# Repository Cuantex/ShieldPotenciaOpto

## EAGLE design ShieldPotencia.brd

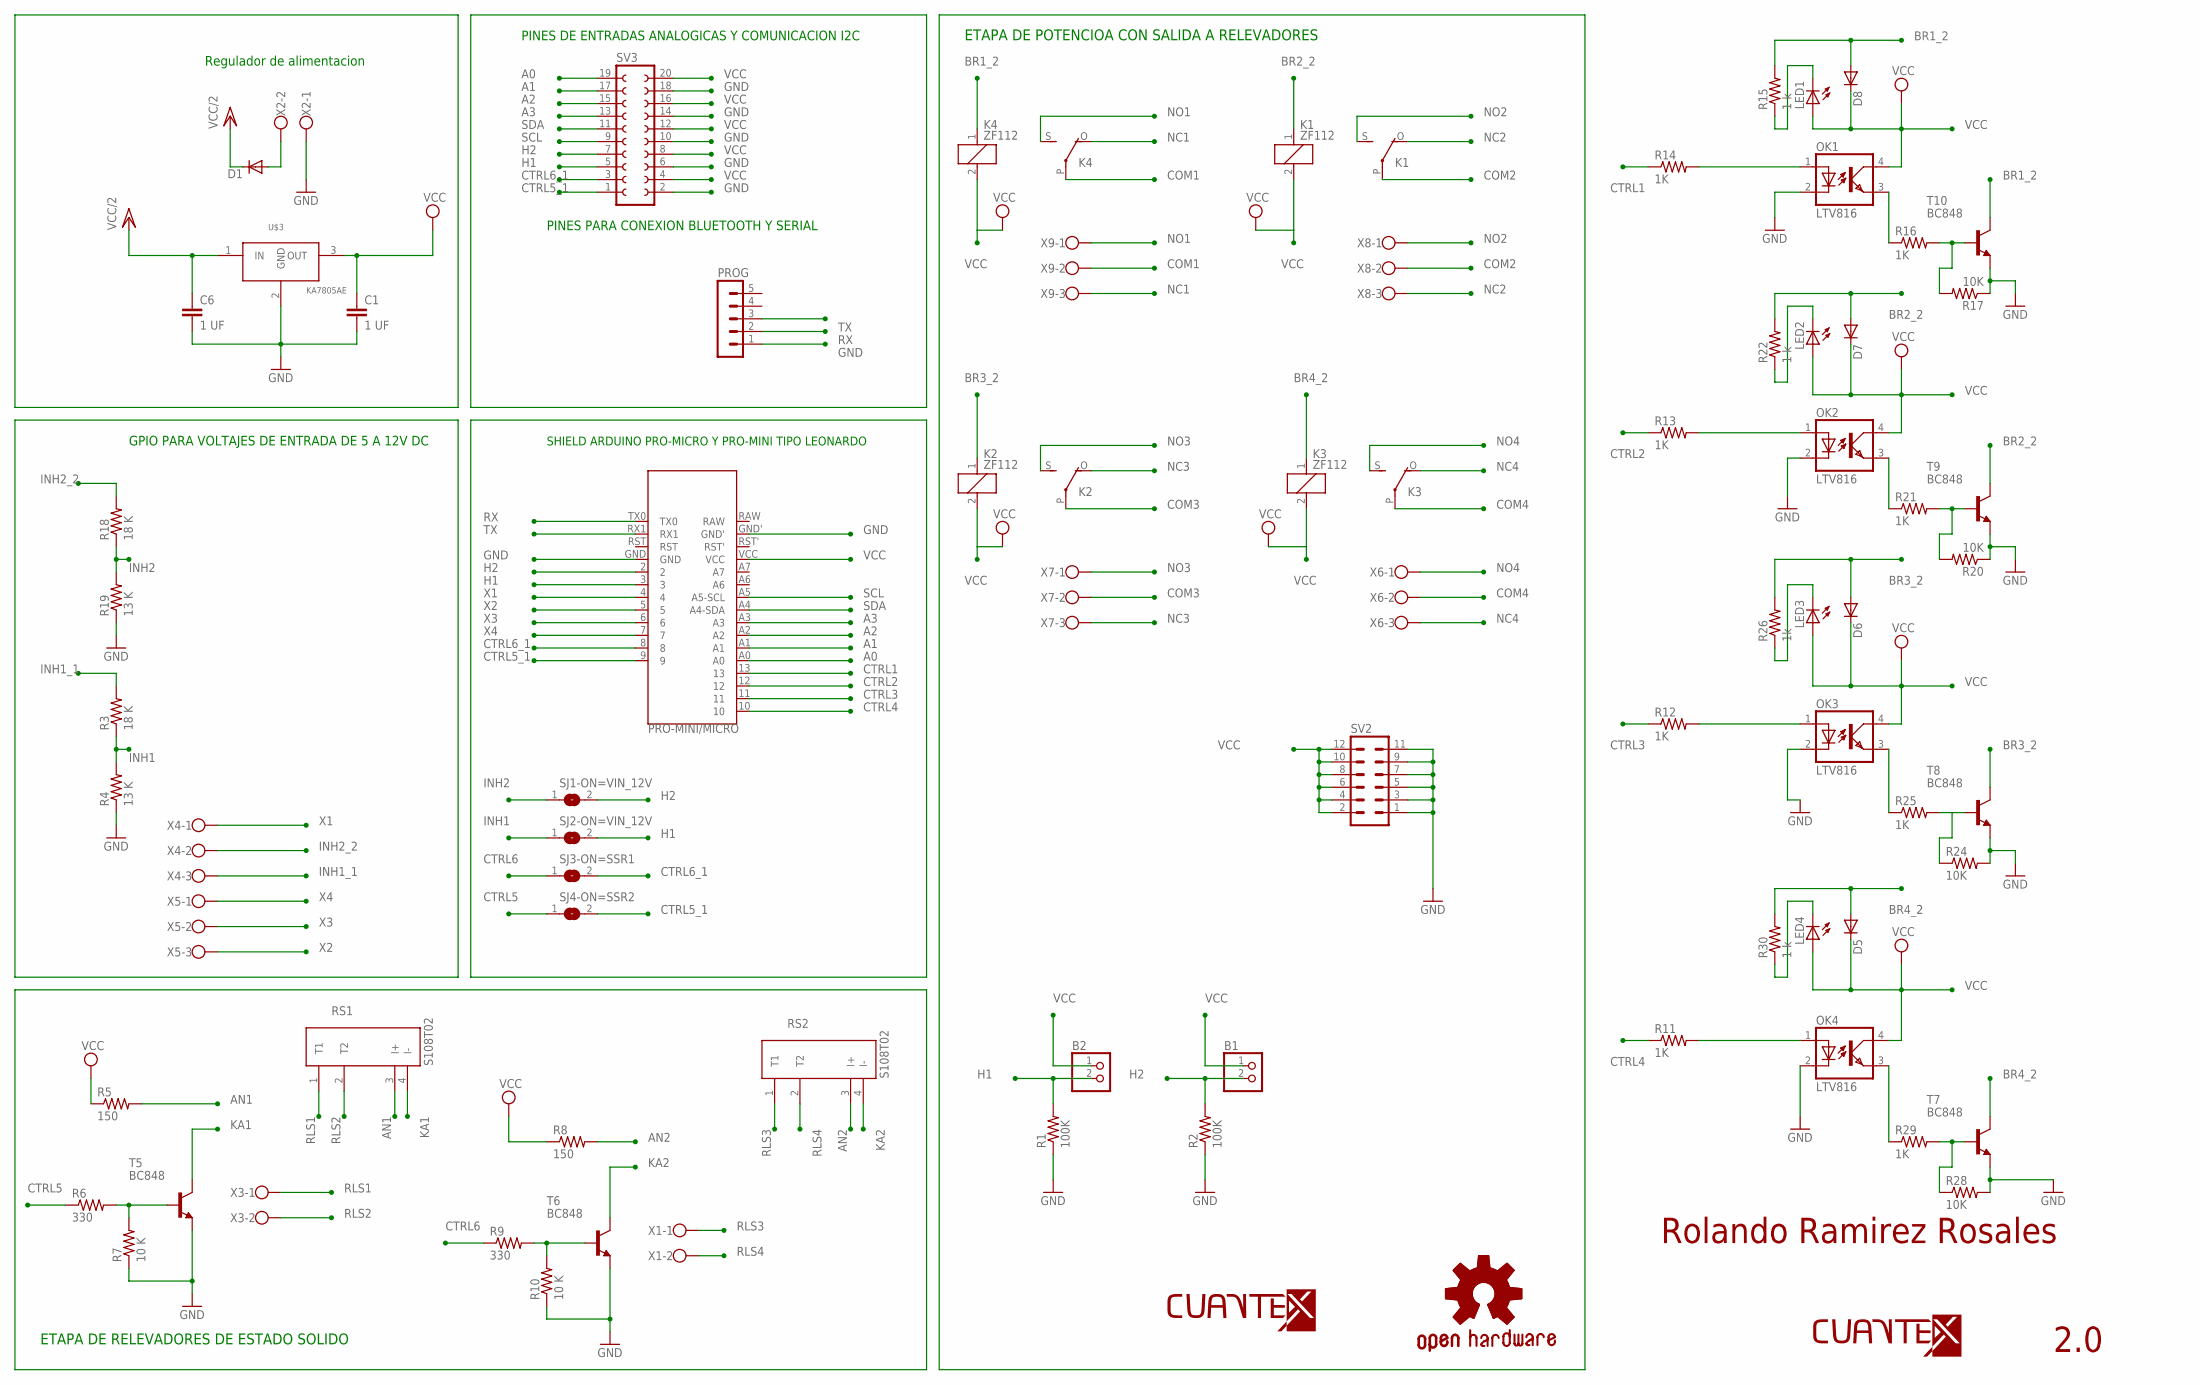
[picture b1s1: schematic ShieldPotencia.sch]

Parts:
B1, B2: PINHD-1X2; 1X02
C1, C6: 1 UF; C0603
D1, D5, D6, D7, D8: DIODE-SMB; SMB
GOLD_ORB_SM1: OSHWLOGO_GOLD_ORB_SM; OSHW2
K1, K2, K3, K4: ZF112
LED1, LED2, LED3, LED4: LED_ESML0603; LED_SML0603
OK1, OK2, OK3, OK4: LTV816; DIL04
PRO-MINI/MICRO: ARDUINO_PRO_MINI_V1
PROG: MA05-1
R1, R2: 100K; R0603
R3, R18: 18 K; R1206
R4, R19: 13 K; R1206
R5, R8: 150; R0603
R6, R9: 330; R0603
R7, R10: 10 K; R0603
R11, R12, R13, R14, R16, R21, R25, R29: 1K; R0603
R15, R22, R30: 1 k; R0603
R17, R20, R24, R28: 10K; R0603
R26: 1k; R0603
RS1, RS2: S108T02; SIP4PIN
SJ1-ON=VIN_12V, SJ2-ON=VIN_12V, SJ3-ON=SSR1, SJ4-ON=SSR2: SJ
SV2: MA06-2
SV3: FE10-2
T5, T6, T7, T8, T9, T10: BC848; SOT23
U$1: LOGO-TOP-50MM; C-3
U$2: LOGO-TOP-20MM; C-0
U$3: KA7805AE; DPAK
X1, X2, X3: W237-102
X4, X5, X6, X7, X8, X9: W237-103

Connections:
A0: PRO-MINI/MICRO.A0, SV3.19
A1: PRO-MINI/MICRO.A1, SV3.17
A2: PRO-MINI/MICRO.A2, SV3.15
A3: PRO-MINI/MICRO.A3, SV3.13
AN1: R5.2, RS1.3 (I+)
AN2: R8.2, RS2.3 (I+)
BR1_2: D8.A, K4.1, R15.2, T10.3 (C)
BR2_2: D7.A, K1.1, R22.2, T9.3 (C)
BR3_2: D6.A, K2.1, R26.2, T8.3 (C)
BR4_2: D5.A, K3.1, R30.2, T7.3 (C)
COM1: K4.P, X9.2
COM2: K1.P, X8.2
COM3: K2.P, X7.2
COM4: K3.P, X6.2
CTRL1: PRO-MINI/MICRO.13, R14.1
CTRL2: PRO-MINI/MICRO.12, R13.1
CTRL3: PRO-MINI/MICRO.11, R12.1
CTRL4: PRO-MINI/MICRO.10, R11.1
CTRL5: R6.1, SJ4-ON=SSR2.1
CTRL5_1: PRO-MINI/MICRO.9, SJ4-ON=SSR2.2, SV3.1
CTRL6: R9.1, SJ3-ON=SSR1.1
CTRL6_1: PRO-MINI/MICRO.8, SJ3-ON=SSR1.2, SV3.3
GND: C1.2, C6.2, OK1.2 (C), OK2.2 (C), OK3.2 (C), OK4.2 (C), PRO-MINI/MICRO.GND, PRO-MINI/MICRO.GND', PROG.1, R1.1, R2.1, R4.1, R7.1, R10.1, R17.1, R19.1, R20.1, R24.2, R28.2, SV2.1, SV2.3, SV2.5, SV2.7, SV2.9, SV2.11, SV3.2, SV3.6, SV3.10, SV3.14, SV3.18, T5.2 (E), T6.2 (E), T7.2 (E), T8.2 (E), T9.2 (E), T10.2 (E), U$3.2 (GND), X2.1
H1: B2.2, PRO-MINI/MICRO.3, R1.2, SJ2-ON=VIN_12V.2, SV3.5
H2: B1.2, PRO-MINI/MICRO.2, R2.2, SJ1-ON=VIN_12V.2, SV3.7
INH1: R3.1, R4.2, SJ2-ON=VIN_12V.1
INH1_1: R3.2, X4.3
INH2: R18.1, R19.2, SJ1-ON=VIN_12V.1
INH2_2: R18.2, X4.2
KA1: RS1.4 (I-), T5.3 (C)
KA2: RS2.4 (I-), T6.3 (C)
unnamed: OK2.1 (A), R13.2
unnamed: R9.2, R10.2, T6.1 (B)
unnamed: LED4.C, R30.1
unnamed: D1.A, X2.2
unnamed: OK4.1 (A), R11.2
unnamed: OK4.3 (EMIT), R29.1
unnamed: R28.1, R29.2, T7.1 (B)
unnamed: R24.1, R25.2, T8.1 (B)
unnamed: OK3.3 (EMIT), R25.1
unnamed: R20.2, R21.2, T9.1 (B)
unnamed: OK2.3 (EMIT), R21.1
unnamed: R16.2, R17.2, T10.1 (B)
unnamed: OK1.3 (EMIT), R16.1
unnamed: LED1.C, R15.1
unnamed: LED2.C, R22.1
unnamed: LED3.C, R26.1
unnamed: OK3.1 (A), R12.2
unnamed: OK1.1 (A), R14.2
unnamed: R6.2, R7.2, T5.1 (B)
NC1: K4.O, X9.3
NC2: K1.O, X8.3
NC3: K2.O, X7.3
NC4: K3.O, X6.3
NO1: K4.S, X9.1
NO2: K1.S, X8.1
NO3: K2.S, X7.1
NO4: K3.S, X6.1
RLS1: RS1.1 (T1), X3.1
RLS2: RS1.2 (T2), X3.2
RLS3: RS2.1 (T1), X1.1
RLS4: RS2.2 (T2), X1.2
RX: PRO-MINI/MICRO.TX0, PROG.2
SCL: PRO-MINI/MICRO.A5 (A5-SCL), SV3.9
SDA: PRO-MINI/MICRO.A4 (A4-SDA), SV3.11
TX: PRO-MINI/MICRO.RX1, PROG.3
VCC: B1.1, B2.1, C1.1, D5.C, D6.C, D7.C, D8.C, K1.2, K2.2, K3.2, K4.2, LED1.A, LED2.A, LED3.A, LED4.A, OK1.4 (COL), OK2.4 (COL), OK3.4 (COL), OK4.4 (COL), PRO-MINI/MICRO.VCC, R5.1, R8.1, SV2.2, SV2.4, SV2.6, SV2.8, SV2.10, SV2.12, SV3.4, SV3.8, SV3.12, SV3.16, SV3.20, U$3.3 (OUT)
VCC/2: C6.1, D1.C, U$3.1 (IN)
X1: PRO-MINI/MICRO.4, X4.1
X2: PRO-MINI/MICRO.5, X5.3
X3: PRO-MINI/MICRO.6, X5.2
X4: PRO-MINI/MICRO.7, X5.1

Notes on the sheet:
Regulador de alimentacion
GPIO PARA VOLTAJES DE ENTRADA DE 5 A 12V DC
ETAPA DE POTENCIOA CON SALIDA A RELEVADORES
PINES DE ENTRADAS ANALOGICAS Y COMUNICACION I2C
PINES PARA CONEXION BLUETOOTH Y SERIAL
SHIELD ARDUINO PRO-MICRO Y PRO-MINI TIPO LEONARDO
ETAPA DE RELEVADORES DE ESTADO SOLIDO
Rolando Ramirez Rosales
2.0

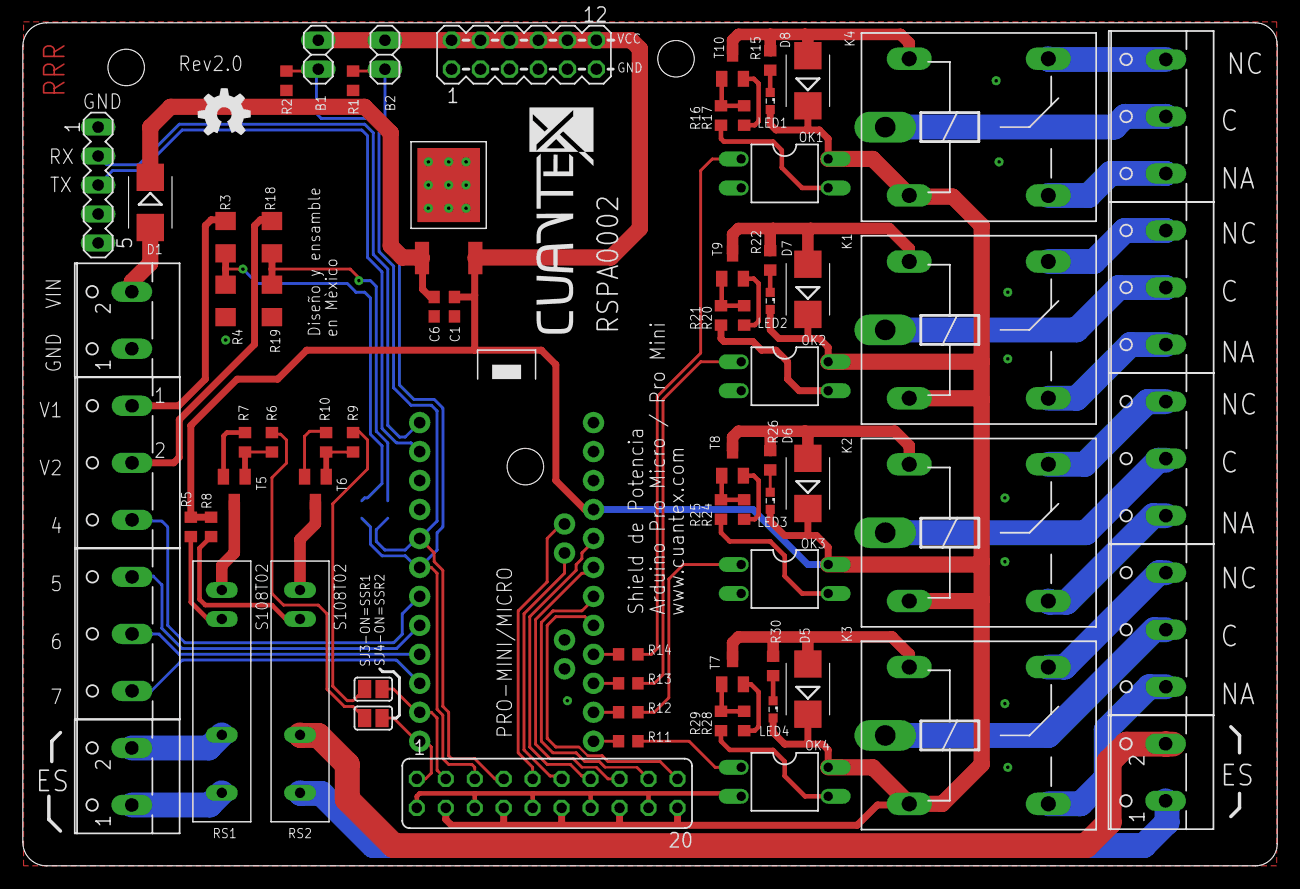
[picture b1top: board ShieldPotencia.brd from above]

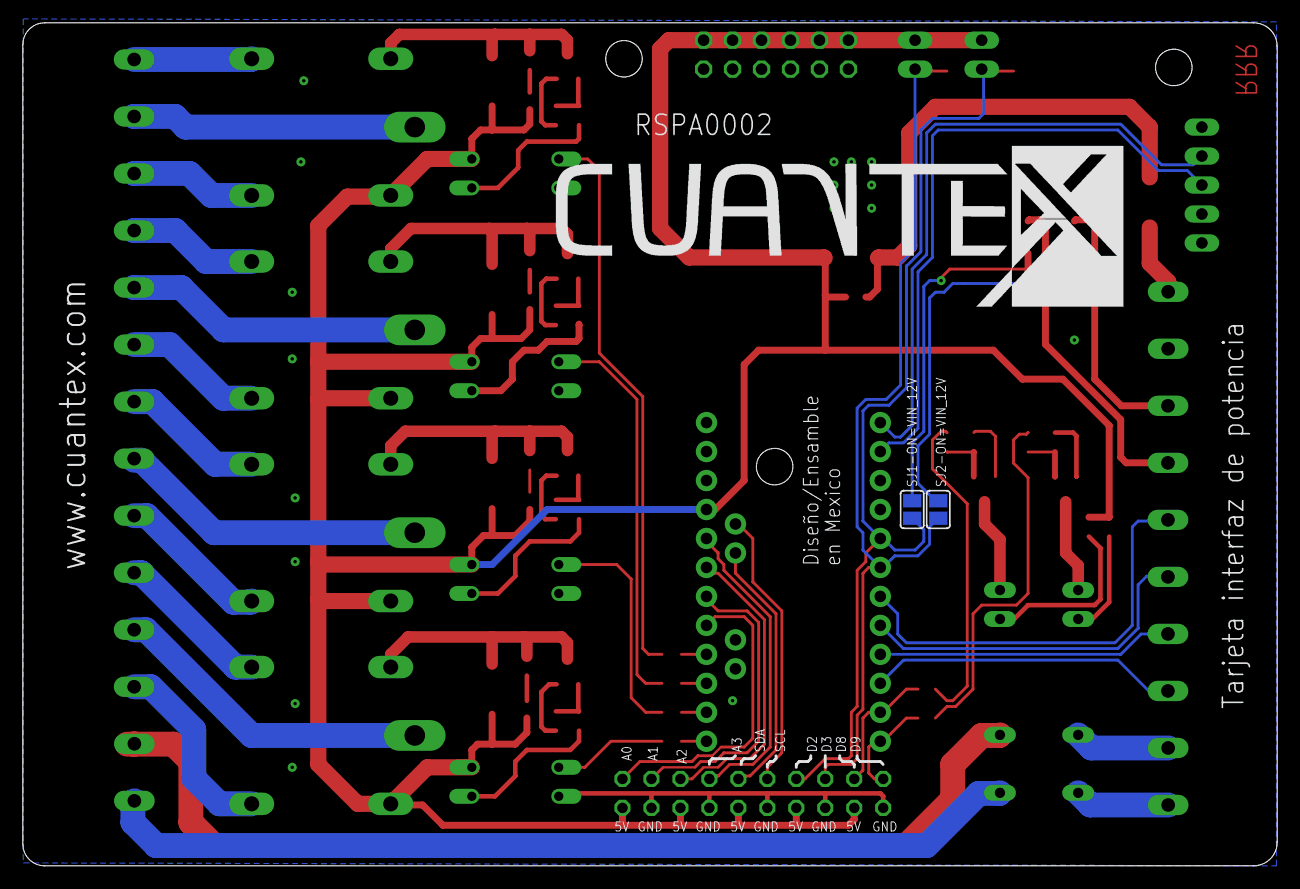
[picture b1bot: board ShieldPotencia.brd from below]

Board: 2 copper layers, 110.0 x 73.9 mm, 78 parts (3 on the bottom side), 72 nets.

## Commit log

2016-10-18 Archivos en Git
